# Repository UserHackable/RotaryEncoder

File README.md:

## Tiny84EncoderReader 

### Board dimensions

* (110000, 110000) original units
* (1.1000, 1.1000) inches
* (27.9400, 27.9400) mm

| Front | Back |
| --- | --- |
|  |  |

## TinyEncoderReader 

### Board dimensions

* (150000, 100000) original units
* (1.5000, 1.0000) inches
* (38.1000, 25.4000) mm

| Front | Back |
| --- | --- |
|  |  |

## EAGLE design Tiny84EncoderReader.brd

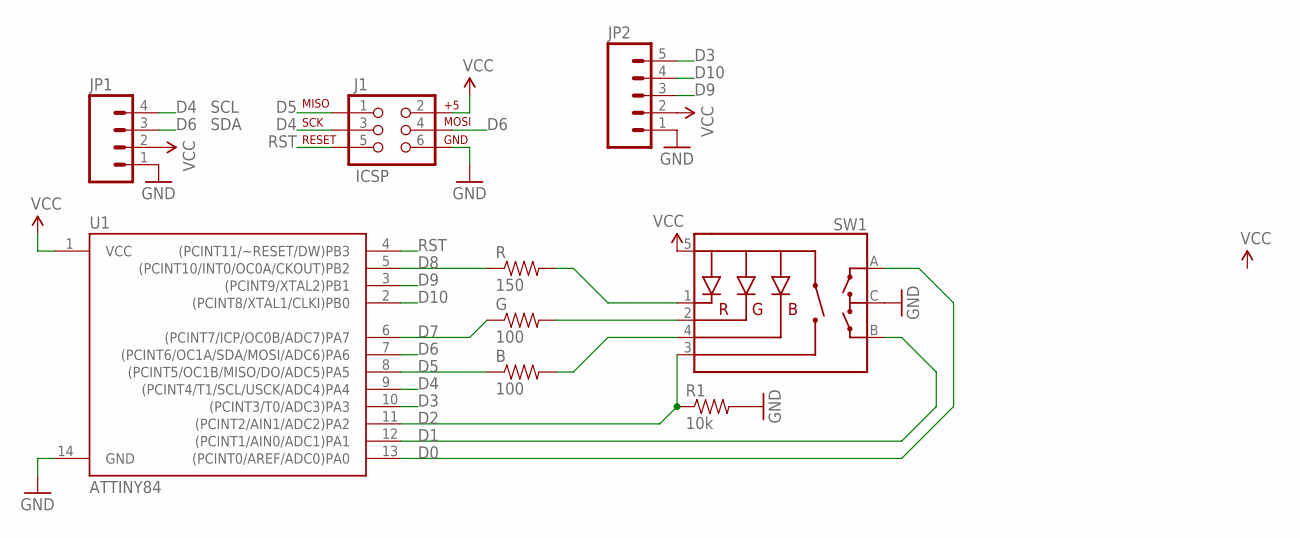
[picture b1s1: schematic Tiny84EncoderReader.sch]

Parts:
B: 100; 0805
G: 100; 0805
J1: ICSP; 2X3-NS
JP1: M04PTH; 1X04
JP2: M05PTH; 1X05
R: 150; 0805
R1: 10k; 0805
SW1: ENCODER_RGB_CA; ENCODER_LED_3
U1: ATTINY84; SO14

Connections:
B: B.2, SW1.4 (-B)
D0: SW1.A, U1.13 ((PCINT0/AREF/ADC0)PA0)
D1: SW1.B, U1.12 ((PCINT1/AIN0/ADC1)PA1)
D2: R1.1, SW1.3 (SW), U1.11 ((PCINT2/AIN1/ADC2)PA2)
D3: JP2.5, U1.10 ((PCINT3/T0/ADC3)PA3)
D4: J1.3 (SCK), JP1.4, U1.9 ((PCINT4/T1/SCL/USCK/ADC4)PA4)
D5: B.1, J1.1 (MISO), U1.8 ((PCINT5/OC1B/MISO/DO/ADC5)PA5)
D6: J1.4 (MOSI), JP1.3, U1.7 ((PCINT6/OC1A/SDA/MOSI/ADC6)PA6)
D7: G.1, U1.6 ((PCINT7/ICP/OC0B/ADC7)PA7)
D8: R.1, U1.5 ((PCINT10/INT0/OC0A/CKOUT)PB2)
D9: JP2.3, U1.3 ((PCINT9/XTAL2)PB1)
D10: JP2.4, U1.2 ((PCINT8/XTAL1/CLKI)PB0)
G: G.2, SW1.2 (-G)
GND: J1.6 (GND), JP1.1, JP2.1, R1.2, SW1.C, U1.14 (GND)
R: R.2, SW1.1 (-R)
RST: J1.5 (RST), U1.4 ((PCINT11/~RESET/DW)PB3)
VCC: J1.2 (V+), JP1.2, JP2.2, SW1.5 (+), U1.1 (VCC)

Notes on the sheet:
SDA
SCL

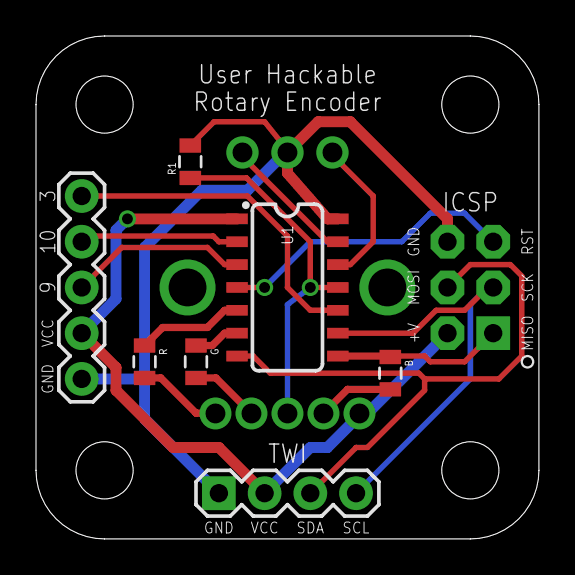
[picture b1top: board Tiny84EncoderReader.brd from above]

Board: 2 copper layers, 27.9 x 27.9 mm, 9 parts (1 on the bottom side), 17 nets.

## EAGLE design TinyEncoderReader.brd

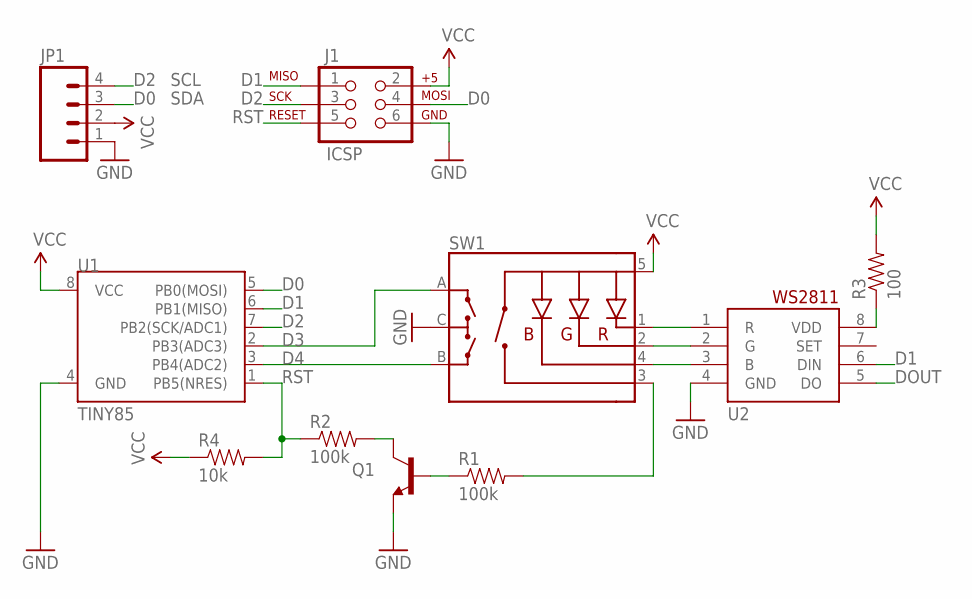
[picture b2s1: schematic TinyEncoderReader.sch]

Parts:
J1: ICSP; 2X3-NS
JP1: M04PTH; 1X04
Q1: TRANSISTOR_NPNTO-92-AMMO; TO-92-AMMO
R1, R2: 100k; AXIAL-0.3
R3: 100; AXIAL-0.3
R4: 10k; AXIAL-0.3
SW1: ENCODER_RGB_CA; ENCODER_LED_3
U1: TINY85; DIP08
U2: WS2811; SO08-SKINNYPADS

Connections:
BLUE: SW1.4 (-B), U2.3 (B)
D0: J1.4 (MOSI), JP1.3, U1.5 (PB0(MOSI))
D1: J1.1 (MISO), U1.6 (PB1(MISO)), U2.6 (DIN)
D2: J1.3 (SCK), JP1.4, U1.7 (PB2(SCK/ADC1))
D3: SW1.A, U1.2 (PB3(ADC3))
D4: SW1.B, U1.3 (PB4(ADC2))
DOUT: U2.5 (DO)
GND: J1.6 (GND), JP1.1, Q1.1 (E), SW1.C, U1.4 (GND), U2.4 (GND)
GREEN: SW1.2 (-G), U2.2 (G)
unnamed: R1.P$2 (2), SW1.3 (SW)
unnamed: Q1.2 (B), R1.P$1 (1)
unnamed: Q1.3 (C), R2.P$2 (2)
RED: SW1.1 (-R), U2.1 (R)
RST: J1.5 (RST), R2.P$1 (1), R4.P$2 (2), U1.1 (PB5(NRES))
VCC: J1.2 (V+), JP1.2, R3.P$2 (2), R4.P$1 (1), SW1.5 (+), U1.8 (VCC)
VDD: R3.P$1 (1), U2.8 (VDD)

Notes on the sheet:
SDA
SCL

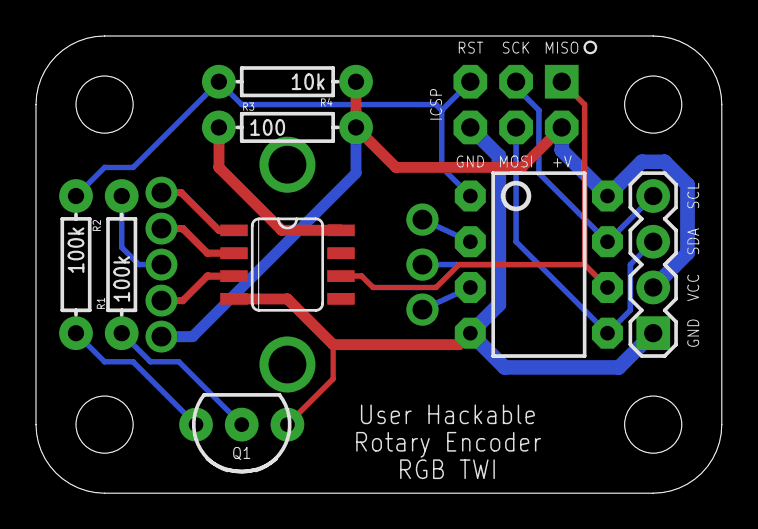
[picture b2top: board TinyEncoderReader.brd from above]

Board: 2 copper layers, 38.1 x 25.4 mm, 10 parts (1 on the bottom side), 15 nets.

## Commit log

2016-04-08 from Makefile

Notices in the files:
parts and their libraries:
SparkFun-Connectors: Licensing: Creative Commons ShareAlike 4.0 International - https://creativecommons.org/licenses/by-sa/4.0
